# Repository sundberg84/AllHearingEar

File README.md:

# AllHearingEar
 
## Slogan (eng)
Open the world for your headphones!
Are you afraid of missing out on something with your headphones covering your ears? 

## Produktbeskrivning (eng)
We believe it’s possible to combine a world with your headphones covering your ears and still not miss anything important happening IRL. Are you a gamer with sleeping children or a reader listening to recorded books and are afraid of missing something is happening? We have the product for you - AllHearingEar! Just because you are covering your ears to fully enjoy your sound should not stop you from hearing a crying baby or a visitor ringing the doorbell. 

The AllHearingEar is always and secure connected to you home Wi-Fi and alerts you with the exact recording in real time. This way you can enjoy your gaming, videos, music or voice with headphones in both ears and still safely know you will be alerted if needed.

The AllHearingEar is a onetime, low-cost hardware you connect to your home Wi-Fi. Free apps and software are downloaded and run in the background of your PC, smartphone or tablet. The software and hardware have a live status and will alert you if disconnected. You have the endless possibility to adjust trigger limits from even the smallest sound to a small orchestra.

All this to be able to enjoy your gaming in full 7.1 sound or a quiet book tucked inside a blanket by the fire - and always know you are in control.

## Idé:
Skapa en babymonitor som ansluter till hemmanätverket via WI-FI och bryter aktivt ljud i din hemdator samt spelar upp ljudet som tas upp av mikrofonen i babymonitorn. 
Detta för att kunna underlätta för användaren av datorn när användaren spelar spel, ser film, lyssnar på musik eller liknande.
Idén uppkom när jag och min bror spelade datorspel tillsammans och båda två var tvungna att sitta med endast en hörlur på ena örat.
Vi vill alltså ha möjlighet att höra våra barn om de eventuellt vaknar, utan att tappa ljud när vi arbetar med våra datorer.

##Namn
Om vi nu ska köra på illuminati pyramid kan vi istället för att produkten heter all-seeing-eye heta all-hearing-ear ?

### Utförande
USB-stick
Pyramid

## Ström?

USB Anslutningar - Konsument står för egna adapters.
Anslutes till telefonladdare - standard USB / MicroUSB.

## Hårdvara

Andreas bygger hårdvara i form av kretskort och mikrofoner. Samt designar ett snyggt och praktiskt hölje!

- Esp8266 Wifi Accesspoint/Server (https://github.com/tzapu/WiFiManager )
- 5V VCC (iphone laddare?) Batteri?
- 3.3V för Esp?
- Electret Microphone Amplifier MAX4466
- Statusled?
- Nattlampa LED

"" PreAmplifier
- OPA3344
https://learn.sparkfun.com/tutorials/electret-mic-breakout-board-hookup-guide
http://www.ti.com/lit/ds/symlink/opa345.pdf

Avoid common problems when designing op-amp and in-amp circuits:
http://www.planetanalog.com/document.asp?doc_id=527560

Div PreAmp
https://arduinodiy.wordpress.com/category/audio/

Noice reduction

General power supply and op-amp noise reduction techniques
http://www.diystompboxes.com/smfforum/index.php?topic=74265.0

Basic Concepts of Designing an RF PCB Board:
https://www.eeweb.com/blog/circuit_projects/basic-concepts-of-designing-an-rf-pcb-board

Small- Signal Audio Design (s.541)
https://books.google.se/books?id=pVIdAAAAQBAJ&pg=PA542&lpg=PA542&dq=microphone+ADC+pcb&source=bl&ots=9AMiR27RV6&sig=jDy-KNQHOQVXisLZhPLIu_6ktNw&hl=sv&sa=X&ved=0ahUKEwjYrtzK87zSAhXLiSwKHYIEA5A4ChDoAQhNMAg#v=onepage&q&f=false

http://www.ti.com/lit/an/szza009/szza009.pdf

https://www.maximintegrated.com/en/app-notes/index.mvp/id/5450

## Skal 
3d pyramid
- 3d printad iluminati pyramid (http://www.shapeways.com/product/G3PZPGYJB/illuminati-flat-peice-v2e)
-Hål undertill för väggfäste!

USB sticka:
- https://stickerapp.se/klistermarken/#!
- http://www.mouser.se/ProductDetail/New-Age-Enclosures/P3A-220805S/?qs=sGAEpiMZZMsrGrAVj6eTvc%252bnjeHQ3V8MaYpIX8AH0%252bY%3d

## Länkar Hårdvara

Microfoner: https://store.invensense.com/ProductDetail/ICS43432-InvenSense-Inc/495200/

https://www.hackster.io/middleca/sending-sound-over-the-internet-f097b4

Https://plus.google.com/wm/1/+MarkChaney/posts/EpTNcAjxMak

https://perso.aquilenet.fr/~sven337/english/2016/07/14/DIY-wifi-baby-monitor.html

#### Ljud/Mic till Arduino:

Https://perso.aquilenet.fr/~sven337/english/2016/07/14/DIY-wifi-baby-monitor.html

https://electronpi.wordpress.com/2013/05/28/getting-going-with-an-electret-microphone-and-an-arduino/
Inkl flera länkar på denna sida!

https://www.youtube.com/watch?v=SToBPCajwc0: Mini project: Amplified electret microphone 

Sök arduino electret microphone circuit

## Wishlist
Kamera

## Mjukvara

Marcus utformar en mjukvara till Windows som synkar hårdvaran och bryter eventuellt ljud som spelas upp från datorn. För att sedan spela upp ljudet från monitorn.
Synkning av hårdvara,
 
Volymkontroll för uppspelning av ljud upptaget av mikrofon, 

Volymkontroll för dämpning av ljud aktiva i PC,
 
Volymkontroll för känslighet i mikrofon,
 
Alternativ för autostart av program (Checkbox),
 
Statusinformation, 

Länk till hemsida.

### Länkar till källor.

https://www.nuget.org/packages/NAudio/1.7.3 (NAudio API för inspelning av ljud i VB)

https://social.msdn.microsoft.com/Forums/vstudio/en-US/c9841350-2d83-4863-b491-6d9f75bb1daa/stream-mic-audio-to-another-computer?forum=vbgeneral (Exempelprogramm för ljudstream via UDP.)

http://www.codeproject.com/Articles/19485/A-Voice-Chat-Application-in-C - A Voice Chat Application in C#

### Wishlist
Knapp för att visa video.
Alternativ för att få video picture in picture när monitor aktiveras.

##Det kommerciella
###Ce/Fee
###Strömadapter
###Förpackning
###Ekonomi
Kickstarter?
###Marknadsföring
Hemsida
Facebook
###Målgrupp
Gamers
Unga med barn
Teknikintresserade (hörlurar) (Sälja hörlurar tillsammans?)
###Användningsområde

Gamers som passar barnen men vill spela
Mammor som lyssnar på ljudböcker? (Kräver app ios/Android?)
Egenföretagare med barn som behöver jobba kväll och vill lyssna på musik.
Studerande med barn som jobbar med datorn och lyssnar på musik.
Musiker som jobbar hemma.
Arbetande tjänstemän som behöver använda en dator i jobbet medans barnen sover.

##Produktbeskrivning/Anvädningsområde
Vi vill alltså ha möjlighet att höra våra barn om de eventuellt vaknar, utan att tappa ljud när vi arbetar med våra datorer.
På ett smart sätt höra din omgivning, exempelvis barn som vaknar, utan att tappa ljud via hörlurarna när man arbetar vid dator/platta/mobil.

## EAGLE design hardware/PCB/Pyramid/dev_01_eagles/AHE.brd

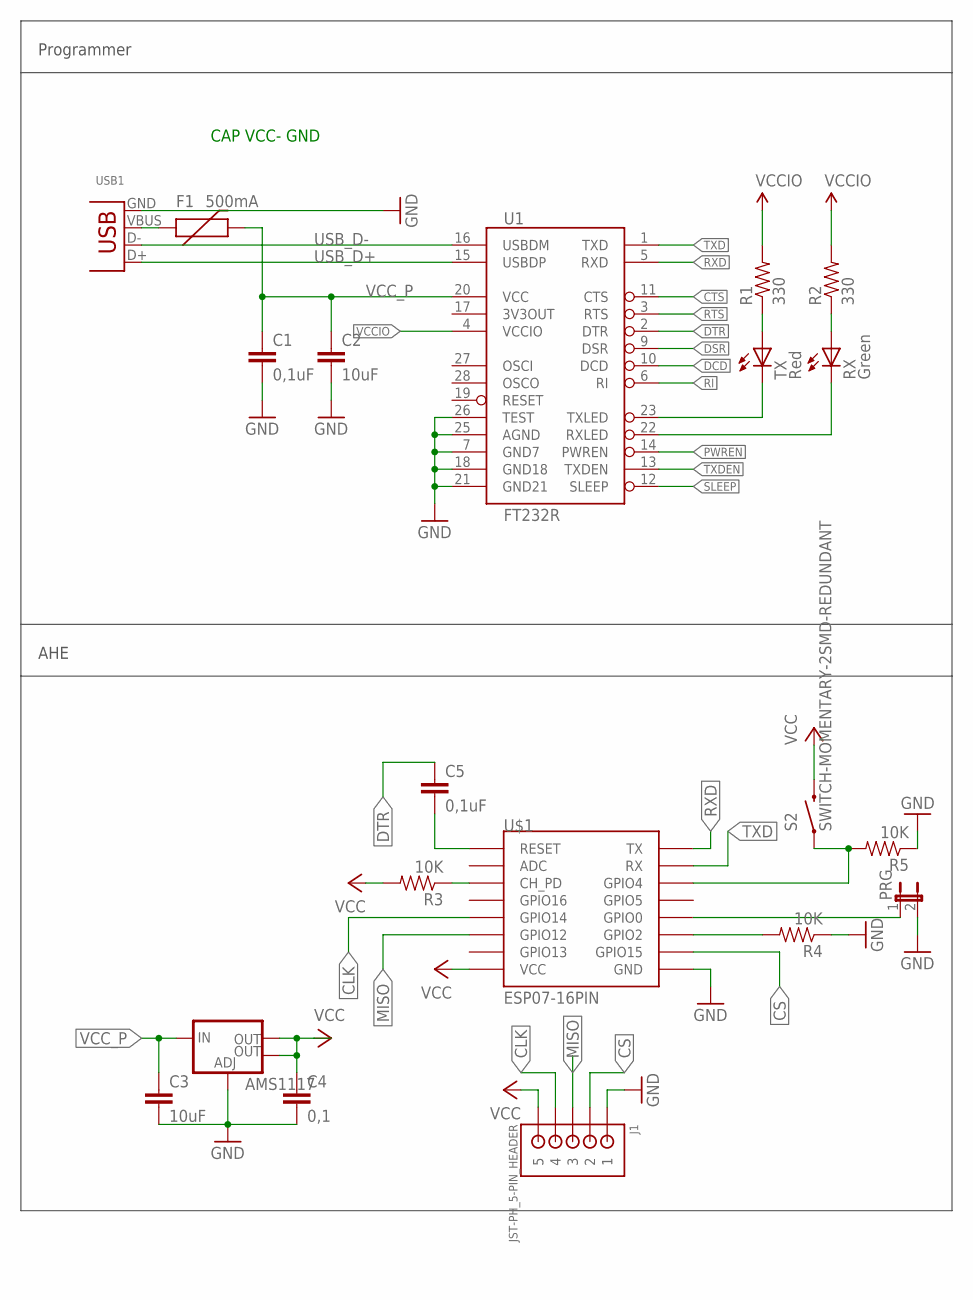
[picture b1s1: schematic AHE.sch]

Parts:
AMS1117: V_REG_LM1117SOT223; SOT223
C1, C5: 0,1uF; 0805-CAP
C2, C3: 10uF; 0805-CAP
C4: 0,1; 0805-CAP
F1: 500mA; PTC-1206
J1: JST-PH_5-PIN_HEADER; JST_B5B-PH_HEADER
PRG: JP1E; JP1
R1, R2: 330; 0805
R3, R4, R5: 10K; 0805
RX: Green; SML0805
S2: SWITCH-MOMENTARY-2SMD-REDUNDANT; TACTILE-SWITCH-SMD
TX: Red; SML0805
U1: FT232R; SSOP28DB
U$1: ESP07-16PIN
USB1: USB-MB-S

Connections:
CLK: J1.P4 (4), U$1.GPIO14
CS: J1.P2 (2), U$1.GPIO15
CTS: U1.11 (CTS)
DCD: U1.10 (DCD)
DSR: U1.9 (DSR)
DTR: C5.1, U1.2 (DTR)
GND: AMS1117.1 (ADJ), C1.2, C2.2, C3.2, C4.2, J1.P1 (1), PRG.2, R4.1, R5.1, U1.7 (GND7), U1.18 (GND18), U1.21 (GND21), U1.25 (AGND), U1.26 (TEST), U$1.GND, USB1.GND
MISO: J1.P3 (3), U$1.GPIO12
unnamed: R1.1, TX.A
unnamed: R2.1, RX.A
unnamed: F1.1, USB1.VBUS
unnamed: R3.1, U$1.CH_PD
unnamed: C5.2, U$1.REST (RESET)
unnamed: R4.2, U$1.GPIO2
unnamed: PRG.1, U$1.GPIO0
unnamed: R5.2, S2.1, S2.2 (1), U$1.GPIO4
PWREN: U1.14 (PWREN)
RI: U1.6 (RI)
RTS: U1.3 (RTS)
RXD: U1.5 (RXD), U$1.TX
RXLED: RX.C, U1.22 (RXLED)
SLEEP: U1.12 (SLEEP)
TXD: U1.1 (TXD), U$1.RX
TXDEN: U1.13 (TXDEN)
TXLED: TX.C, U1.23 (TXLED)
USB_D+: U1.15 (USBDP), USB1.D+
USB_D-: U1.16 (USBDM), USB1.D-
VCC: AMS1117.2 (OUT), AMS1117.4 (OUT), C4.1, J1.P5 (5), R3.2, S2.3 (2), S2.4 (2), U$1.VCC
VCCIO: R1.2, R2.2, U1.4 (VCCIO)
VCC_P: AMS1117.3 (IN), C1.1, C2.1, C3.1, F1.2, U1.20 (VCC)

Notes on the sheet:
Programmer
AHE
CAP VCC- GND

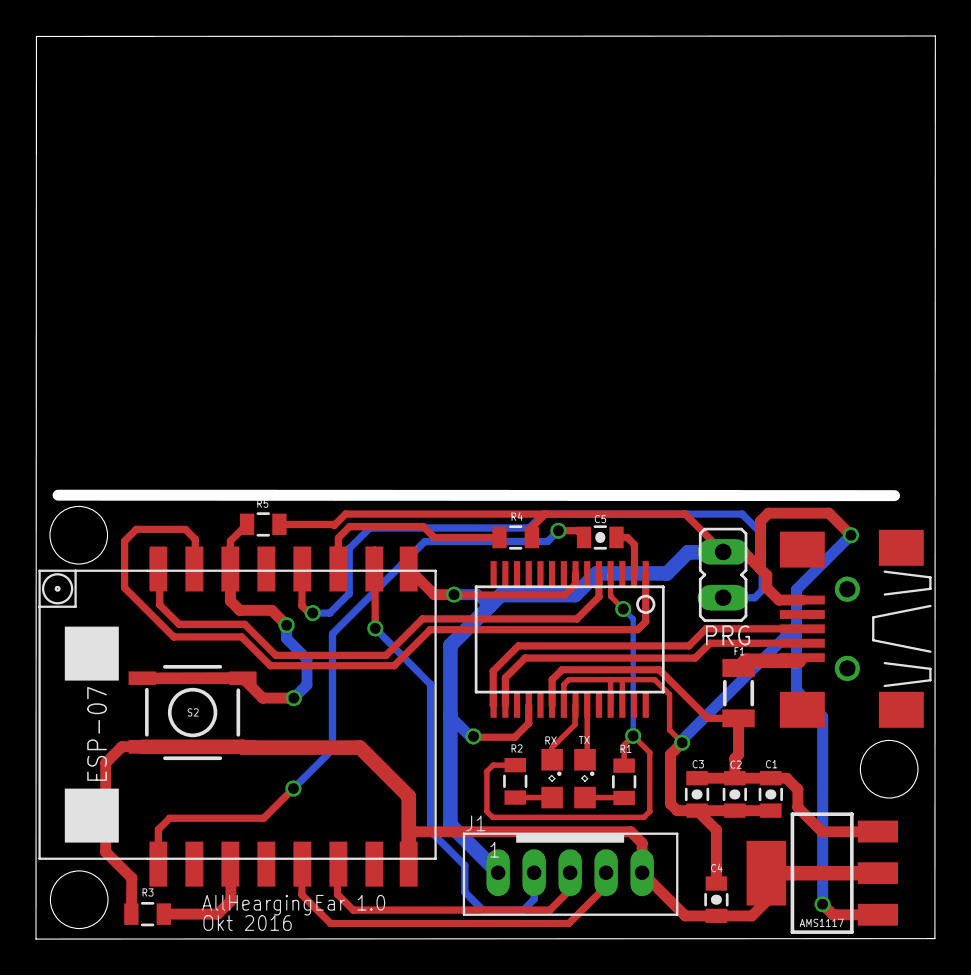
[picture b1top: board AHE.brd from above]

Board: 2 copper layers, 49.4 x 49.6 mm, 20 parts (0 on the bottom side), 22 nets.

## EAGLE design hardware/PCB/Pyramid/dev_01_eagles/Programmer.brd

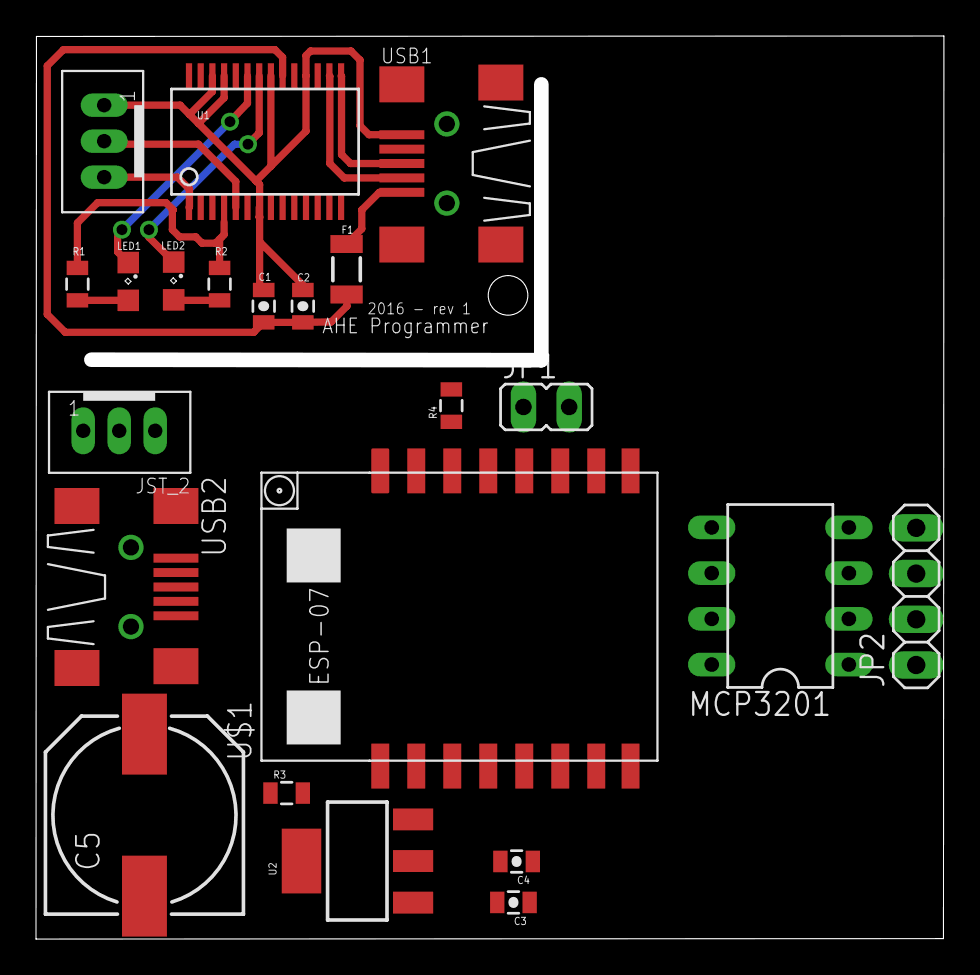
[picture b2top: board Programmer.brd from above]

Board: 2 copper layers, 49.6 x 49.4 mm, 22 parts (0 on the bottom side), 25 nets.

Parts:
C1, C4: 0,1; 0805-CAP
C2, C3: 10uF; 0805-CAP
C5: 100uF; NIC_10X10.5_CAP
F1: 500mA; PTC-1206
JP1: JP1
JP2: 1X04
JST_1, JST_2: JST_B3B-PH_HEADER
LED1: Red; SML0805
LED2: Green; SML0805
MCP3201: DIL08
R1, R2: 330; 0805
R3, R4: 10K; 0805
U1: FT232R; SSOP28DB
U2: SOT223
U$1: ESP07-16PIN
USB1, USB2: USB-MB-S

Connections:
5V: C3.1, C5.+, U2.3, USB2.VBUS
AN+: JP2.2, MCP3201.2
AN-: JP2.3, MCP3201.3
CLK: MCP3201.7, U$1.GPIO14
CS: MCP3201.5, U$1.GPIO15
GND: C1.2, C2.2, JST_1.P1, U1.7, U1.18, U1.21, U1.25, U1.26, USB1.GND
GND2: C3.2, C4.2, C5.-, JP1.2, JP2.4, JST_2.P1, MCP3201.4, R4.1, U2.1, U$1.GND, USB2.GND
MISO: MCP3201.6, U$1.GPIO12
unnamed: LED1.A, R1.1
unnamed: LED2.A, R2.1
unnamed: F1.1, USB1.VBUS
unnamed: R3.1, U$1.CH_PD
unnamed: JST_2.P2, U$1.TX
unnamed: R4.2, U$1.GPIO2
unnamed: JP1.1, U$1.GPIO0
unnamed: JST_2.P3, U$1.RX
RXD: JST_1.P2, U1.5
RXLED: LED2.C, U1.22
TXD: JST_1.P3, U1.1
TXLED: LED1.C, U1.23
USB_D+: U1.15, USB1.D+
USB_D-: U1.16, USB1.D-
VCC: C4.1, JP2.1, MCP3201.1, MCP3201.8, R3.2, U2.2, U2.4, U$1.VCC
VCCIO: R1.2, R2.2, U1.4
VCC_P: C1.1, C2.1, F1.2, U1.20

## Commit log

2016-09-13 Smändringar
    Gjort lite ändringar i readme
2016-09-13 Laddat upp projekt.
    Laddat upp projekt för mjukvara.
2016-09-13 Picture
    Försöker sätta ihop skiten.
2016-09-13 ESP Info
    Sparad info för hur ESP ska kopplas
2016-09-15 UDPTest
    UDP test sketch
2016-09-16 AC/DC samt UDP test
    Readme, frågeställning om ström
    Vidareut av IDP test sketch.
2016-09-18 Uppdaterat Readme
    Uppdaterat readmefil med mina ändringar och länkar till de källor jag
    använt.
2016-09-18 Uppdaterad källkod.
    Uppdaterad källkod av mjukvara som kan ta emot ljud och text via
    UPDprotkoll.
2016-09-18 Icon och loggfunktion
    Lyckades skapa en fungerande loggfunktion som loggar samtliga händelser
    i programmet genom en ConStat() funktion:) Även uppdaterat Readme.
2016-09-18 Små uppdateringar
    Iconen fixad. Autostartfunktion(Checkbox) fungerar felfritt.
2016-09-18 core.ino
    Börjat bygga huvudfilen
2016-09-19 Uppdatering länk
    Uppdatering länk
2016-09-19 Readme
2016-09-19 Fortsätning på core.
2016-09-20 Sortering och sync
    Har gjort en logik för att kunna synka upp till fyra enheter.
    I nuläget kan man synka samma enhet flera gånger. Löses enkelt.
2016-09-21 Synken funkar!!!
    Nu kan jag synca 4 enheter! Samma enhet kan bara synkas en gång. Man kan
    namge sin enhet och man kan glömma den igen! Allt sparas i
    applikationen!
    Nästa steg är att filtrera och visa vilken enhet som sänder!
2016-09-25 Status på individuella AHE.
    Du ser status och loggar de olika AHE-enheterna. Du har alltså kolla på
    vilken du är ansluten till eller om du tappar anslutning till någon av
    de synkade enheterna.
2016-09-29 Mellanupload
    Inget spec, bara synd
2016-10-04 Update 4 okt
    Kicad och folder changes
2016-10-08 Inför träff
    Alla ändringar inför träff
2016-10-13 Senaste uppdateringarna
    Inte mycket nytt men en fräsch sync.
2016-10-15 Ändrat lite värden för bättre ljud.
    Se titel.
2016-10-15 Ljudet fungerar!
    Ljud fungerar-
2016-10-16 Uppdaterat 3dmodel
    Uppdaterat 3dmodel
2016-10-17 PCB klar
    PCB Klar, vb moduler klara, 3d ritning uppdaterad.
2016-10-18 Snyggare layout
    Snyggare layout
2016-10-18 Försöker få rätt sync
    Försöker få rätt sync
2016-10-18 Fräsch commit
    3dmodel och rätt kod
2016-10-18 Tisdagscommit
2016-10-18 Model uppdaterad
    Michål och usbhål samt "balja" till kretskort
2016-10-20 Uppdatering av 3dkretskort
    Exaktare mått för 3d modellen kretskortet.
2016-10-20 PCB arbete och bilder
    Fortsätter PCB, ny två paneler. Lite nya bilder tagna på arbetet.
2016-10-20 Uppdaterad FindSlot och Sync fungerar
    Sync funkar nu med timer. Ska flyttas över till Whileloop?
    FindSlot & SyncNew fungerar. Ska flyttas till modul?
2016-10-21 Ny uppdelning Audio och Commands
    Döpt om lite variabler för att särskilja Audio mottagaren och commands sändare/mottagare.
2016-10-21 Infotext
    Infotext
2016-10-21 Senaste synk
    Små uppdateringar
2016-10-21 UDPModul - Logfunktion
    UDPModul - Logfunktion
2016-10-21 Lägger till main för ref
    Lägger till main för ref
2016-10-22 addLog
2016-11-01 UDPServer
    Hela UDP Server projecktet
2016-11-07 Ny programvara som fungerar.
    Gjort om projektet. Implemeterat Andreas UDPkodning.
2016-11-08 Amplifier PCB
2016-11-08 Pyramid02
2016-11-08 Mappändringar
2016-11-08 Volymkontroller och buggar
    Fungerande känslighetsinställningar för varje AHE.
    Buggfix: Synca samma enhet på samma slot om du tagit bort den precis.
    Smått ändrat utseende.
2016-11-16 0.2 update
2016-11-16 Bilder till 02
2016-11-16 Ny Pyramid
    Helt ny model.
    endast 8x8 i basen istället för 10x10. Lite lägre.
    Rätt mått på micingång, väggfäste samt USBingång.
    Annan infästning mellan lock och bas.
    Lite bredare "skål" för kretskortet.
2016-11-17 Uppdaterat pyramid 0.3
    USBhålet bör fungera... bör...
2016-11-20 Nästan färdig prototyp.-
    Du bör kolla om USBhålet stämmer. Måtten bör vara bra men du bör mäta så
    att positionen stämmer.
2016-11-21 Nya fäste för lock/botten
    Ändrat till gammal variant
2016-11-22 0.4 & 0.4.1
    Nya modeller uppe.
2016-11-23 Pyramid04 3dprint format
    90kr/st
2016-11-25 Dev05 och Excel for alla nr
2016-11-27 Pyramid0.5
    Ladduttaget är mätt på rätt sätt. Med hänsyn till marginaler. Har gjort
    en skalenlig 3dLaddare att testa med. SKA fungera!
2016-11-27 Senaste AHE mjukvaran
    Känslighet för AHEhårdvara samt mastervolymkontroll(som inte fungerar
    än)
2016-11-27 Funkar hos Marcus
2016-11-28 Dev10 PCB
2016-11-30 UDP recieve Change
2016-11-30 Nya framgångar skördas
2016-12-01 AHE161201
    Syncar senaste arbetet.
2016-12-02 Tillägg debugline
    Andreas
2016-12-02 Användbar mjukvara!!!!
    #Syncar AHE och börjar lyssna vid uppstart.
    #Startar UDPAudioThread endast om där finns syncade enheter.
    #Manuell Sync
    #Buggfix i pingfunktion.
    #Nödping om ej svar.
2016-12-03 Ljuduppdatering
    Uppdatering av audio.
2016-12-03 Ljudkontroll
    Ljudkontroll fungerar.
    Sparar senaste inställningen.
    Startar UDP vid rätt tillfälle.
    Ett fel som Andreas kan lösa i UDPmodulen.?
2016-12-04 Senaste ändringar.
2016-12-04 Uppdatering av audiomodul
    Grymt mycket bättre ljud!
2016-12-04 Bajs - missade dessa.
2016-12-05 Ny test
2016-12-08 Hårdvarustädning
    Städning mappar, USB Sticka ny!
2016-12-10 Start och stop av ljud funkar!!
    Nu fungerar det!
    Sista innan 1.0 är syncen i början. Hur får vi fram vilken IP mjukvaran
    ska synca till!?
    Även en färdig Pyramid syncad!
2016-12-14 Hårdvara
2016-12-17 Dev06
2016-12-18 Bandlås
2016-12-18 Småändringar
    Enterknappar och isntallationsfil
2016-12-18 USB Sticka 3D
    Dev 06 + 3d modell usb
2016-12-28 MicroUSB
2016-12-28 MicroUsbCorr
2016-12-28 MicroCorr
2016-12-28 Corr25typ
2016-12-31 Tagit bort onödiga saker
2016-12-31 VoipTest
2016-12-31 Länk
2017-01-01 SyncDev7
2017-01-01 Fungerande utan klick på gammal HW
    Ändrat källkod i UDPmodul och Augiomodul. Funkar utan klick på HW.
2017-01-03 Update README.md
    Länk
2017-01-03 Sticker for 3dmodell
2017-01-03 Lite Div
2017-01-08 Uppdateringar
    ClearSync, AndroidAPP och senaste 3dmodelen
2017-01-08 Androidapp
    Fungerar förhoppningsvis nåt sånär bra.
2017-01-09 Firmware07 and Pics
2017-01-10 Buggfixar i Android
    Fixat Sync vid start. Syncknappen, manuell sync. Notification och ikon.
    Tangentbordet försvinner vid "OK" på mansync.
2017-01-10 Pics
2017-01-10 Notiser fungerar
    som dom ska? (Ikonen syns bara när man får en notis?)
2017-01-11 Android GUI test
    Androididé
2017-01-21 Ny preamplifier
2017-01-22 StickUppdatering
2017-01-30 Uppdatering av SeekBar i appen och debug
    Finns seekbar (Borde fungera) och debug.
    Debug i PC genom att dubbelklicka på "Sensitivity labeln".
    Debug i Android genom att longklicka på logon.
2017-01-30 New hardware
2017-02-01 Fräsh update
    Borde funka med setup
2017-03-02 NewPCB Things
2017-06-01 Dev08
2017-11-11 Create Note2As
2017-11-12 Update Note2As

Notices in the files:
parts and their libraries:
SparkFun-Capacitors: Licensing: CC v3.0 Share-Alike You are welcome to use this library for commercial purposes.
SparkFun-Resistors: Licensing: Creative Commons ShareAlike 4.0 International - https://creativecommons.org/licenses/by-sa/4.0
